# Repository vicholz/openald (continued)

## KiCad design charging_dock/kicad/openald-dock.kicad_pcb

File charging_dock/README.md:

# OpenALD Dock v1.0 — 6-slot USB-C charging dock

A charging dock for six OpenALD radios (2 rows × 3). Each radio stands USB-C-end down in a printed pocket that is
**2.00 in (50.8 mm) deep**, so the level-bar LEDs stay visible. A lead-in chamfer and a tight 0.35 mm guide zone at
the bottom centre the radio's USB-C receptacle on a vertical USB-C plug. **One USB-C PD input at the rear centre**
powers all six slots.

> **Status: design only, nothing here is hardware-validated.** ERC/DRC are clean and the CAD fit check passes, but no
> board has been built, no charger has been tested, and the plug height and insertion have not been measured on a
> real part. Treat the first build as a prototype.

Both radio variants fit the same pockets (`radio_single_board`, and `radio_adafruit_feather_rp2040` if it keeps the
lower envelope). The exact interface is in **[DOCK_INTERFACE.md](DOCK_INTERFACE.md)**.

**Plug depth (2026-11-12, still v1.0):** both radios now have their USB-C mouth **1.60 mm inside the bottom face** (the
Feather since commit 1452af8; the single board since its J1 moved 0.9 mm toward the board edge). The floor pads are
**4.00 mm** (were 3.10) and the PCB standoffs **4.1 mm** (were 5.0), so the plug goes **6.0 mm** past the mouth on both
radios (USB-C full seat 6.20 ± 0.20) while the outer size, the 50.8 mm pocket and the deck height stay the same. The
short-lived Feather riser shims (commit 0ba4451) are gone. Section view: `previews/dock_plug_insertion_per_radio.png`.
**Radios built before this change** (single board with J1 flush to the board edge, mouth 2.50) would only get 5.1 mm in this dock.

## Key numbers
| | |
|---|---|
| Outer size | **191.8 × 111.7 × 62.5 mm** (W × D × H) |
| Spacing | **25.4 mm (1.0 in)** between radios, in both X and Y |
| Pocket | 50.8 deep; 0.35 mm/side clearance for the bottom 12 mm, 0.60 above; 3 mm 45° lead-in; power-switch knob relief slot in the right wall |
| PCB | 186.0 × 105.9 mm, 2-layer, 1.6 mm, all SMT parts on top |
| Minimum charger | **USB-C PD, 45 W: must offer 20 V ≥ 2.25 A or 15 V ≥ 3 A** |
| Per-slot limit | ~1.45 A (1.09–1.81 A, SY6280 ±25 %), 5.10 V |
| Print bed | needs ≥ 192 × 112 mm for the top shell (fits 220 × 220 beds; not an A1 mini) |

## Power architecture
```
USB-C IN (J1, HRO TYPE-C-31-M-12, CC1/CC2 -> HUSB238)
  -> F1 4 A fuse (0466004.NRHF) -> D1 SMBJ22A TVS -> C1 10 uF 50 V
  -> Q1 AO4407A P-FET input switch (gate: R2 100k / R3 47k / C3 4.7 nF soft turn-on, driven by HUSB238 GATE; opens on OVP)
  -> VIN_SW, C4 100 uF 35 V
     -> U2 SY8205FCC buck A (4.7 uH MWSA0604S, 3x22 uF + 470 uF, 75k/10k -> 5.10 V) -> slots 1, 2, 4
     -> U3 SY8205FCC buck B (same)                                                   -> slots 3, 5, 6
        each slot: SY6280AAC current-limited switch (Rset 4.7k -> ~1.45 A) + 10 uF -> vertical plug VBUS,
        22k Rp on CC ("default USB power" to the radio's 5.1k Rd), plug GND + shell to GND
Status LED (light pipe in the deck between the centre pockets): green = 5 V up; red = input present but no usable PD
```
* **HUSB238** (VSET open = request up to 20 V, ISET 13.7k = 2.25 A) picks the highest PDO ≤ 20 V that offers ≥ 2.25 A,
  otherwise it steps down. D+/D− are left open (PD only).
* **Buck enable threshold:** EN divider 100k/12k from VIN_SW. The bucks turn on at 11.2–13.1 V (typ. 12.1 V). **5 V and
  9 V never enable them** (non-PD or 5 V-only chargers are safe: the dock stays off with the red LED lit). 15 V and
  20 V always enable them. **12 V-only chargers are not supported** (they may or may not start).
* Worst-case load is 6 × ~0.95 A × 5.1 V ≈ 29 W. At 20 V/2.25 A (45 W) there is about 35 % headroom after converter
  losses. Each buck is rated 5 A and carries ≤ 3 radios.

| Part | LCSC | Stock (2026-11-11 PST) | Unit |
|---|---|---|---|
| HUSB238_002DD PD sink | C7471904 | 17,771 | $0.47 |
| SY8205FCC buck ×2 | C111875 | 10,557 | $0.34 |
| SY6280AAC slot switch ×6 | C55136 | 97,877 | $0.09 |
| AO4407A input P-FET | C16072 | 19,166 | $0.33 |
| MWSA0604S-4R7MT 4.7 µH 7 A ×2 | C408457 | 8,136 | $0.17 |
| 0466004.NRHF 4 A fuse | C187596 | 14,764 | $0.08 |
| SMBJ22A TVS | C151920 | 7,664 | $0.07 |
| 100 µF 35 V / 470 µF 10 V electrolytic | C2895269 / C2858856 | 5,149 / 138,705 | $0.12 / $0.05 |
| HRO TYPE-C-31-M-12 input receptacle | C165948 | 281,637 | $0.19 |
| HX TYPE C-M 16P V-SMT vertical plug ×6 (hand solder) | C55200592 | **782** | $0.54 |

The full list is in `fab/openald-dock-BOM-human.csv` (live stock and price); `fab/cost_estimate.txt` has the cost estimate.

## Files
| Path | What |
|---|---|
| `kicad/openald-dock.kicad_{pro,sch,pcb}` | KiCad 9 project (schematic and board are generated by the scripts) |
| `fab/openald-dock-gerbers-jlcpcb.zip` | Gerbers + drill (JLCPCB) |
| `fab/openald-dock-BOM-jlcpcb.csv`, `fab/openald-dock-CPL-jlcpcb.csv` | JLC assembly BOM + CPL (JLC_CORR rotation/offset corrections applied) |
| `fab/openald-dock-centroid.csv`, `fab/openald-dock.pos` | Centroid / KiCad position files |
| `fab/openald-dock-BOM-human.csv`, `fab/cost_estimate.txt`, `fab/lcsc_lookup.json` | Human BOM with live stock and prices, cost estimate |
| `fab/erc_report.txt`, `fab/drc_report.txt`, `fab/jlc_cpl_fit.json` | Check reports |
| `case/openald_dock.scad`, `case/dock_params.scad` | OpenSCAD case (parameters generated from the PCB layout) |
| `case/dock_top_shell.stl`, `case/dock_base.stl`, `case/dock_floor_pads_x6.stl`, `case/floor_pads/*.stl` | Print-ready STLs (already in print orientation) |
| `case/dock_fit_report.txt` | Fit-check result |
| `docs/openald-dock-schematic.pdf`, `previews/*.png` | Schematic PDF, PCB/case renders, CPL overlay plots |
| `scripts/` | Generators: `run_all_pcb.sh` (symbols → schematic → ERC → board → route → post-route → DRC), `make_fab.py`, `jlc_cpl_fit.py`, `build_case.sh`, `check_dock_fit.py`, `render_pcb_previews.py`; `geom.py` is the single source of the geometry |

## Checks (2026-11-11)
* **ERC:** 0 errors, 0 warnings.
* **DRC:** 0 errors, **0 unconnected**. 75 silkscreen-only warnings (reference text overlapping copper, other silk or the board edge; cosmetic).
* **JLC placement:** `jlc_cpl_fit.py --check` → *correction table: OK*. All 80 CPL rows match the EasyEDA footprints' pads; worst pad-centre offset is 0.29 mm (SY8205 land-length difference). Overlays are in `previews/cpl_overlay_*.png`.
* **Case fit:** `case/dock_fit_report.txt` → **INTERFERENCES: 0**. This covers radio envelopes vs. shell/pads/base, plugs vs. case and radios (the plug sits inside the USB-C cavity), the PCB with its holes vs. every case part, every PCB part vs. every case part, and the case parts against each other. The closest part to the shell is the D3 LED, 0.19 mm under the light pipe. Insertion is 6.0 mm. The report lists the insertion per radio (6.00 / 6.00) and the Z stack.

## Printing (no supports)
* **Top shell:** print it deck-down, as exported. Walls, bosses, the light pipe and the pocket tubes grow straight up. The lead-in chamfers are 45°. Vent slots and the rear USB-C opening bridge ≤ 13 mm.
* **Base:** print it flat, as exported.
* **Floor pads (6):** print them top-face down, as exported (pegs up). Slot 5 (back centre) has its own STL with a relief over the rear USB-C receptacle's pads. The pads are interchangeable otherwise, but `floor_pads/` has one file per slot.
* PETG or PLA, 0.2 mm layers, 3 walls. Check the pocket guide on one radio before printing all six pads. If the fit is tight, the guide clearance is `CLR_GUIDE` in `scripts/geom.py`.

## Assembly
1. **Order the PCB** with JLC SMT assembly (gerber zip + BOM + CPL). The six vertical plugs J2–J7 are **not** in the JLC BOM, because LCSC has no EasyEDA footprint for C55200592 and JLC cannot verify its placement. Buy 6 (+1 spare) from LCSC and hand-solder them. They are 16 fine-pitch (0.8 mm) SMD pads plus 2 plated shell slots: use flux, a fine tip or hot air, and keep each plug **vertical** (a printed floor pad slipped over it works as a jig).
2. **Test before docking a radio:** plug in a ≥ 45 W PD charger. Green should light and red should stay off. Each slot should read 5.0–5.2 V on VBUS. A 5 V-only charger should give red only, with no slot voltage.
3. Press 6 M3 heat-set inserts into the shell bosses. Lay the PCB on the base standoffs and drop the six floor pads in (the pegs go into the PCB holes). Lower the shell over everything and fit 6 × **M3 × 10** screws from below (the standoffs are 4.1 mm since 2026-11-12; M3 × 12 would bottom out in the 6.5 mm insert holes).
4. Dock a radio front face (level-bar side) toward you, wheel to the right.

## Open risks and judgment calls
* **Plug height and insertion are not measured.** The HX drawing gives 11.60 (used here, 6.0 mm insertion) but also a 12.50 overall (possibly including the shell tabs that go through the board; not confirmed). Measure a soldered plug from the PCB top. If it is taller, the radios would stand on the plug: make `PAD_T` thicker and `STANDOFF` thinner by the difference in `scripts/geom.py` and rebuild (shorter screws again).
* **Receptacle depth:** the real seat depth of the HRO and CUI receptacles isn't on their drawings; 6.20 ± 0.20 is the USB-C spec value. Both radios must keep the 1.60 mm mouth; an older single board (mouth 2.50) only gets 5.1 mm.
* **Hand-soldered plugs:** fine pitch, and the plug must be perpendicular. The 0.35 mm guide clearance plus the case opening tolerate only ~0.5 mm of plug misalignment.
* **Plug supply:** only 782 in stock at LCSC, and it is the only in-stock vertical (board-mount, plug-up) USB-C plug found with a usable drawing. Buy spares early.
* **12 V fallback:** 12 V-only chargers are deliberately not supported. A 30 W charger that offers 12 V/2.5 A may or may not start the dock and could overload with six radios charging.
* **Autorouted power layout:** routing is Freerouting plus scripted widening of the high-current tracks (up to 2 mm) and GND pours on both layers. Review the buck hot loops (C11/C12 → U2/U3 → GND) in `previews/pcb_copper_*.png` before ordering.
* **Heat:** six radios charging inside 2 in pockets. Each pocket wall has vent slots into the open channels, and the deck and base are vented, but there is no fan. Watch radio temperature on the first full charge.
* **Viewing angle:** the single-board radio's level bar is centred on its front face, its three windows 27.0 / 29.8 / 32.6 mm above the rim (2026-11-11 update; see `DOCK_INTERFACE.md` §1). The back-row bars are best read from above or from the front at a downward angle.
* **While docked:** the radio's own TP4056 charge LEDs (D3/D4, near the USB end) are hidden. Charging is shown on the level bar by firmware (it reads CHRG_SENSE). The power switch is not reachable while docked; the relief slot in the right wall only clears the knob so it isn't flipped by insertion.
* **Layout margins:** the back margin is 13.5 mm (instead of 6) to fit the rear USB-C receptacle behind the back-centre pocket. The 25.4 mm spacing leaves channels wide enough for the electronics.
* **Not validated:** HUSB238 negotiation, buck stability with the chosen compensation (internal), SY6280 limits, thermals and plug mating are all untested.

## History
* v1.0 (2026-11-11): first design. The project was renamed from OpenALS to OpenALD before release, so the dock was born as "OpenALD Dock v1.0".

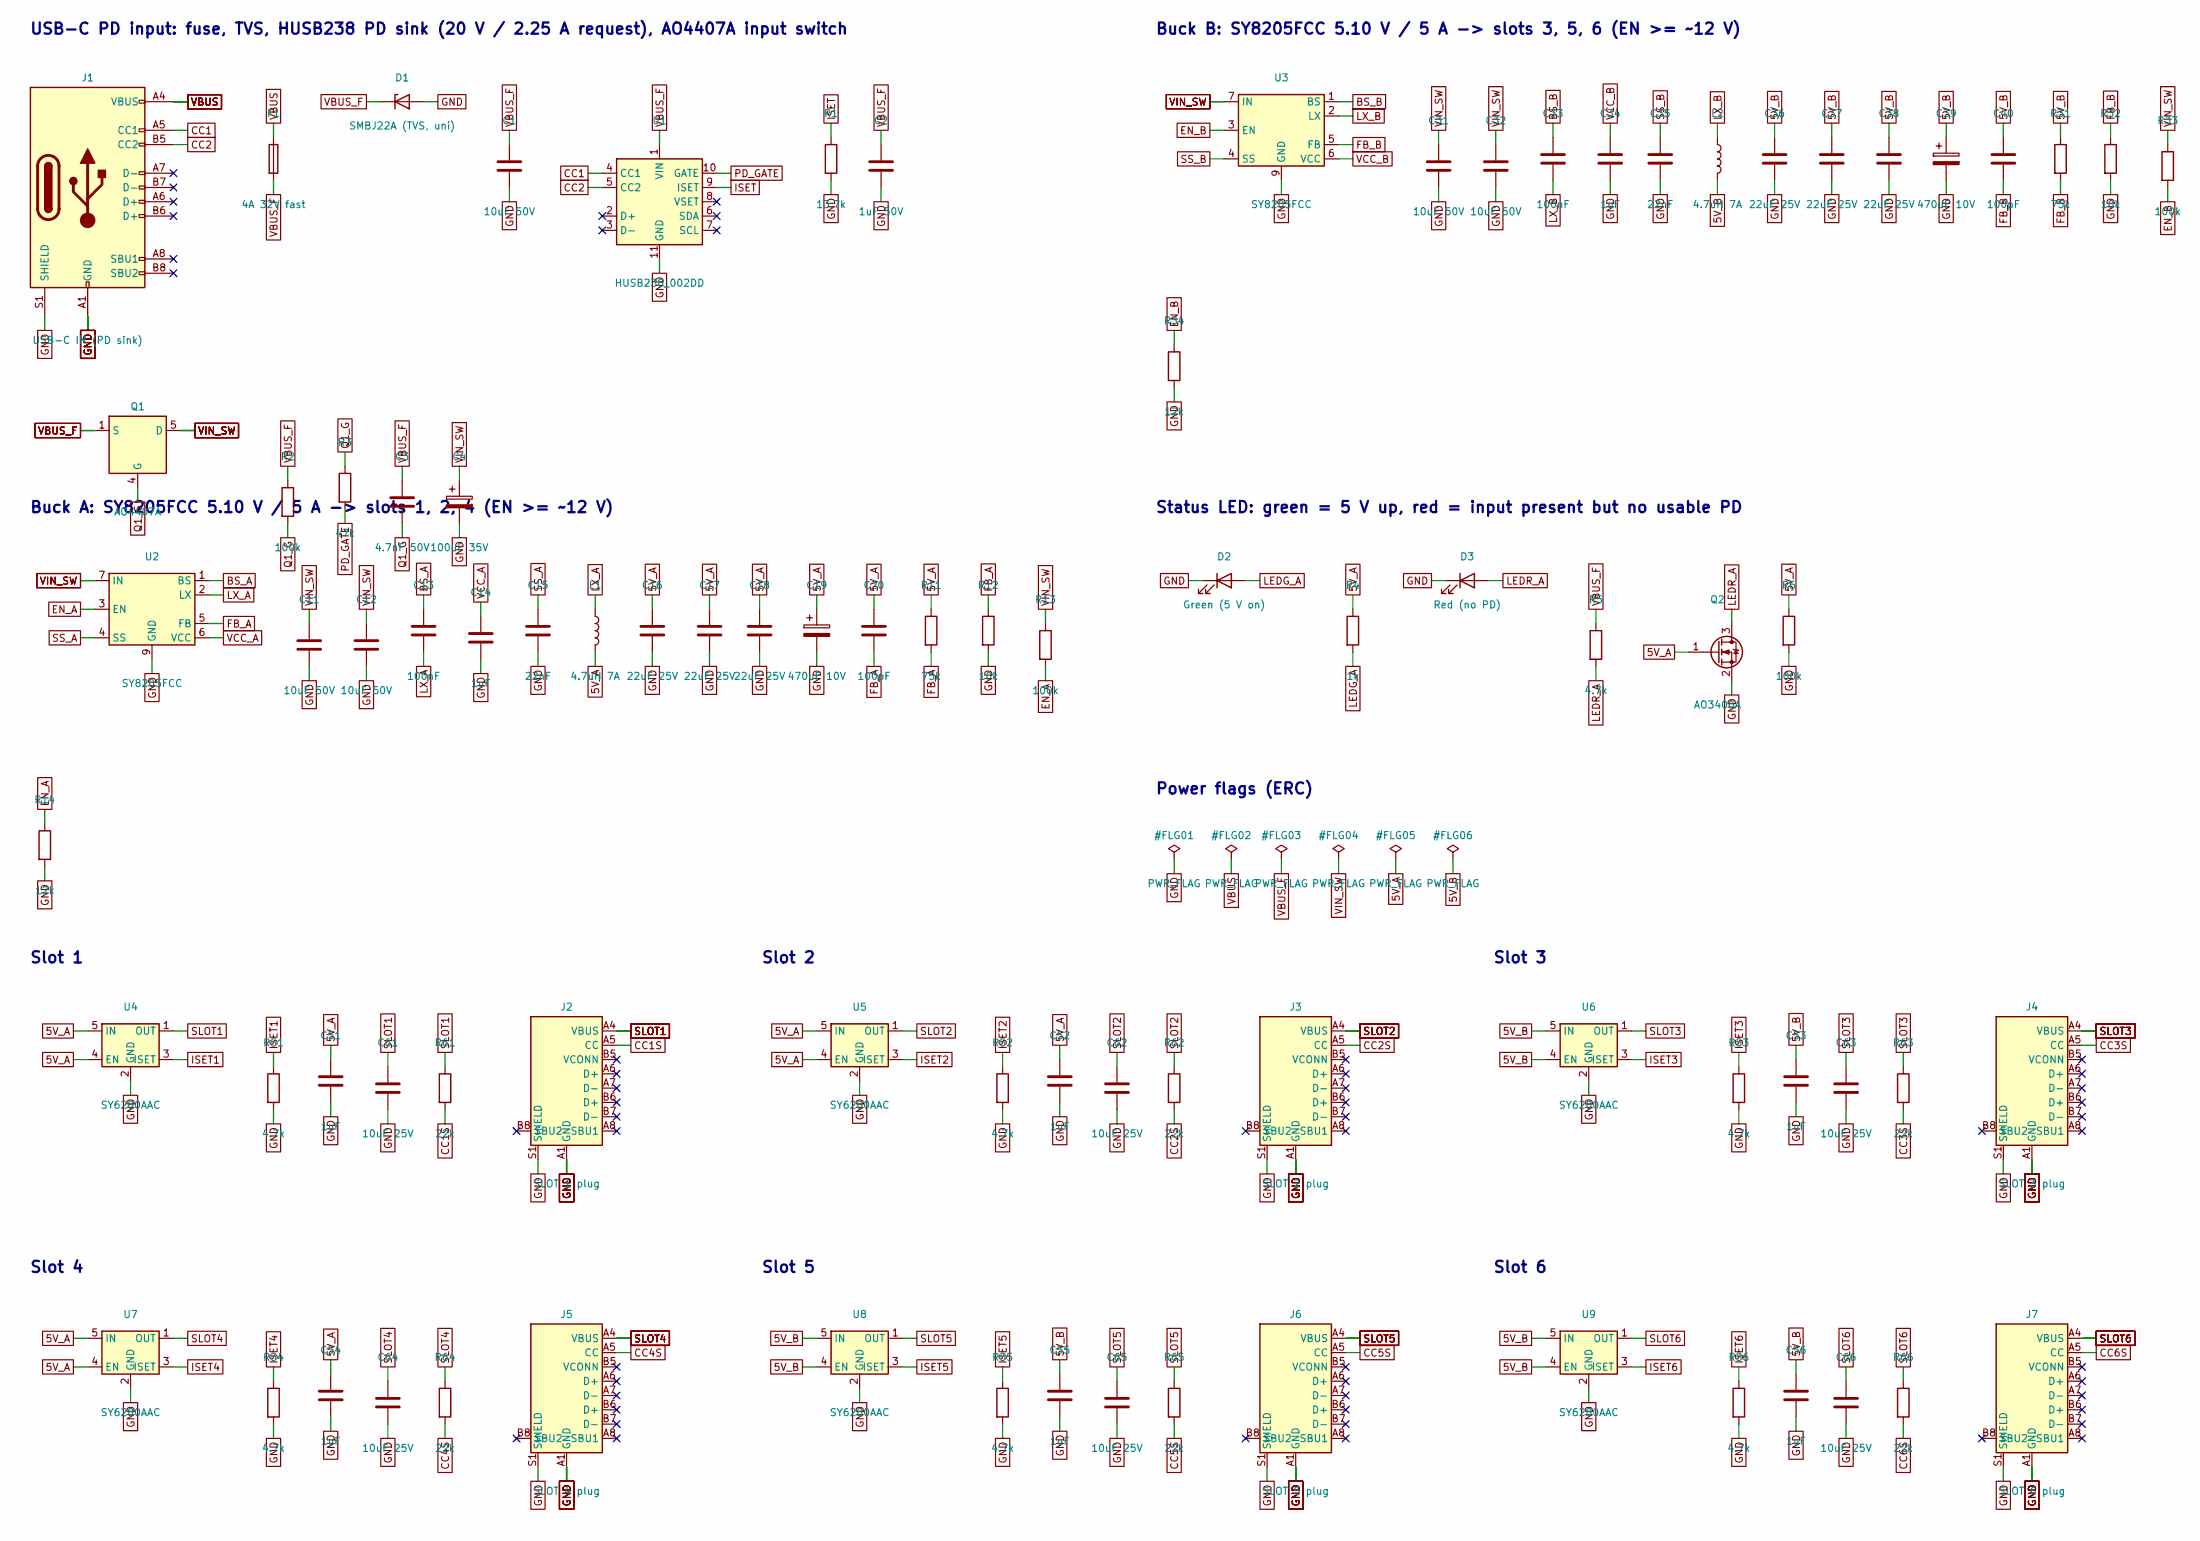
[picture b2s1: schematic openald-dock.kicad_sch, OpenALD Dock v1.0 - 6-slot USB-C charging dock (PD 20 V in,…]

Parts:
C1, C11, C12, C31, C32: 10uF 50V; C_1206_3216Metric; MPN CL31A106KBHNNNE; LCSC C13585
C2: 1uF 50V; C_0603_1608Metric; MPN CL10A105KB8NNNC; LCSC C15849
C3: 4.7nF 50V; C_0603_1608Metric; MPN 0603B472K500NT; LCSC C53987
C4: 100uF 35V; CP_Elec_8x10; MPN RVE100UF35V67RV0161; LCSC C2895269
C13, C33: 100nF; C_0603_1608Metric; MPN CC0603KRX7R9BB104; LCSC C14663
C14, C34, C51, C52, C53, C54, C55, C56: 1uF; C_0603_1608Metric; MPN CL10A105KB8NNNC; LCSC C15849
C15, C35: 22nF; C_0603_1608Metric; MPN CL10B223KB8NNNC; LCSC C21122
C16, C17, C18, C36, C37, C38: 22uF 25V; C_0805_2012Metric; MPN CL21A226MAQNNNE; LCSC C45783
C19, C39: 470uF 10V; CP_Elec_6.3x7.7; MPN RVT470UF10V67RV0159; LCSC C2858856
C20, C40: 100pF; C_0603_1608Metric; MPN CL10C101JB8NNNC; LCSC C14858
C61, C62, C63, C64, C65, C66: 10uF 25V; C_0805_2012Metric; MPN CL21A106KAYNNNE; LCSC C15850
D1: SMBJ22A (TVS, uni); D_SMB; MPN SMBJ22A; LCSC C151920
D2: Green (5 V on); LED_0603_1608Metric; MPN KT-0603G; LCSC C12624
D3: Red (no PD); LED_0603_1608Metric; MPN KT-0603R; LCSC C2286
F1: 4A 32V fast; Fuse_1206_3216Metric; MPN Littelfuse 0466004.NRHF; LCSC C187596
J1: USB-C IN (PD sink); USB_C_Receptacle_HRO_TYPE-C-31-M-12; MPN HRO TYPE-C-31-M-12; LCSC C165948
J2: SLOT 1 plug; USB_C_Plug_HX_TYPE-C-M-16P_Vertical; MPN HX TYPE C-M 16P V-SMT; LCSC C55200592
J3: SLOT 2 plug; USB_C_Plug_HX_TYPE-C-M-16P_Vertical; MPN HX TYPE C-M 16P V-SMT; LCSC C55200592
J4: SLOT 3 plug; USB_C_Plug_HX_TYPE-C-M-16P_Vertical; MPN HX TYPE C-M 16P V-SMT; LCSC C55200592
J5: SLOT 4 plug; USB_C_Plug_HX_TYPE-C-M-16P_Vertical; MPN HX TYPE C-M 16P V-SMT; LCSC C55200592
J6: SLOT 5 plug; USB_C_Plug_HX_TYPE-C-M-16P_Vertical; MPN HX TYPE C-M 16P V-SMT; LCSC C55200592
J7: SLOT 6 plug; USB_C_Plug_HX_TYPE-C-M-16P_Vertical; MPN HX TYPE C-M 16P V-SMT; LCSC C55200592
L1, L2: 4.7uH 7A; L_Sunlord_MWSA0604S; MPN Sunlord MWSA0604S-4R7MT; LCSC C408457
Q1: AO4407A; SOIC-8_3.9x4.9mm_P1.27mm; MPN AOS AO4407A; LCSC C16072
Q2: AO3400A; SOT-23; MPN AOS AO3400A; LCSC C20917
R1: 13.7k; R_0603_1608Metric; MPN 0603WAF1372T5E; LCSC C22793
R2, R6, R13, R33: 100k; R_0603_1608Metric; MPN 0603WAF1003T5E; LCSC C25803
R3: 47k; R_0603_1608Metric; MPN 0603WAF4702T5E; LCSC C25819
R4: 1k; R_0603_1608Metric; MPN 0603WAF1001T5E; LCSC C21190
R5: 4.7k; R_0805_2012Metric; MPN 0805W8F4701T5E; LCSC C17673
R11, R31: 75k; R_0603_1608Metric; MPN 0603WAF7502T5E; LCSC C23242
R12, R32: 10k; R_0603_1608Metric; MPN 0603WAF1002T5E; LCSC C25804
R14, R34: 12k; R_0603_1608Metric; MPN 0603WAF1202T5E; LCSC C22790
R51, R52, R53, R54, R55, R56: 4.7k; R_0603_1608Metric; MPN 0603WAF4701T5E; LCSC C23162
R61, R62, R63, R64, R65, R66: 22k; R_0603_1608Metric; MPN 0603WAF2202T5E; LCSC C31850
U1: HUSB238_002DD; DFN-10-1EP_3x3mm_P0.5mm_EP1.55x2.48mm; MPN Hynetek HUSB238_002DD; LCSC C7471904
U2, U3: SY8205FCC; SOIC-8-1EP_3.9x4.9mm_P1.27mm_EP2.29x3mm; MPN Silergy SY8205FCC; LCSC C111875
U4, U5, U6, U7, U8, U9: SY6280AAC; SOT-23-5; MPN Silergy SY6280AAC; LCSC C55136

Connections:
5V_A: C16.1, C17.1, C18.1, C19.1, C20.1, C51.1, C52.1, C54.1, L1.2, Q2.1 (G), R4.1, R6.1, R11.1, U4.4 (EN), U4.5 (IN), U5.4 (EN), U5.5 (IN), U7.4 (EN), U7.5 (IN)
5V_B: C36.1, C37.1, C38.1, C39.1, C40.1, C53.1, C55.1, C56.1, L2.2, R31.1, U6.4 (EN), U6.5 (IN), U8.4 (EN), U8.5 (IN), U9.4 (EN), U9.5 (IN)
BS_A: C13.1, U2.1 (BS)
BS_B: C33.1, U3.1 (BS)
CC1: J1.A5 (CC1), U1.4 (CC1)
CC1S: J2.A5 (CC), R61.2
CC2: J1.B5 (CC2), U1.5 (CC2)
CC2S: J3.A5 (CC), R62.2
CC3S: J4.A5 (CC), R63.2
CC4S: J5.A5 (CC), R64.2
CC5S: J6.A5 (CC), R65.2
CC6S: J7.A5 (CC), R66.2
EN_A: R13.2, R14.1, U2.3 (EN)
EN_B: R33.2, R34.1, U3.3 (EN)
FB_A: C20.2, R11.2, R12.1, U2.5 (FB)
FB_B: C40.2, R31.2, R32.1, U3.5 (FB)
GND: C1.2, C2.2, C4.2, C11.2, C12.2, C14.2, C15.2, C16.2, C17.2, C18.2, C19.2, C31.2, C32.2, C34.2, C35.2, C36.2, C37.2, C38.2, C39.2, C51.2, C52.2, C53.2, C54.2, C55.2, C56.2, C61.2, C62.2, C63.2, C64.2, C65.2, C66.2, D1.2 (A), D2.1 (K), D3.1 (K), J1.A1 (GND), J1.A12 (GND), J1.B1 (GND), J1.B12 (GND), J1.S1 (SHIELD), J2.A1 (GND), J2.A12 (GND), J2.B1 (GND), J2.B12 (GND), J2.S1 (SHIELD), J3.A1 (GND), J3.A12 (GND), J3.B1 (GND), J3.B12 (GND), J3.S1 (SHIELD), J4.A1 (GND), J4.A12 (GND), J4.B1 (GND), J4.B12 (GND), J4.S1 (SHIELD), J5.A1 (GND), J5.A12 (GND), J5.B1 (GND), J5.B12 (GND), J5.S1 (SHIELD), J6.A1 (GND), J6.A12 (GND), J6.B1 (GND), J6.B12 (GND), J6.S1 (SHIELD), J7.A1 (GND), J7.A12 (GND), J7.B1 (GND), J7.B12 (GND), J7.S1 (SHIELD), Q2.2 (S), R1.2, R6.2, R12.2, R14.2, R32.2, R34.2, R51.2, R52.2, R53.2, R54.2, R55.2, R56.2, U1.11 (GND), U2.9 (GND), U3.9 (GND), U4.2 (GND), U5.2 (GND), U6.2 (GND), U7.2 (GND), U8.2 (GND), U9.2 (GND)
ISET: R1.1, U1.9 (ISET)
ISET1: R51.1, U4.3 (ISET)
ISET2: R52.1, U5.3 (ISET)
ISET3: R53.1, U6.3 (ISET)
ISET4: R54.1, U7.3 (ISET)
ISET5: R55.1, U8.3 (ISET)
ISET6: R56.1, U9.3 (ISET)
LEDG_A: D2.2 (A), R4.2
LEDR_A: D3.2 (A), Q2.3 (D), R5.2
LX_A: C13.2, L1.1, U2.2 (LX)
LX_B: C33.2, L2.1, U3.2 (LX)
PD_GATE: R3.2, U1.10 (GATE)
Q1_G: C3.2, Q1.4 (G), R2.2, R3.1
SLOT1: C61.1, J2.A4 (VBUS), J2.A9 (VBUS), J2.B4 (VBUS), J2.B9 (VBUS), R61.1, U4.1 (OUT)
SLOT2: C62.1, J3.A4 (VBUS), J3.A9 (VBUS), J3.B4 (VBUS), J3.B9 (VBUS), R62.1, U5.1 (OUT)
SLOT3: C63.1, J4.A4 (VBUS), J4.A9 (VBUS), J4.B4 (VBUS), J4.B9 (VBUS), R63.1, U6.1 (OUT)
SLOT4: C64.1, J5.A4 (VBUS), J5.A9 (VBUS), J5.B4 (VBUS), J5.B9 (VBUS), R64.1, U7.1 (OUT)
SLOT5: C65.1, J6.A4 (VBUS), J6.A9 (VBUS), J6.B4 (VBUS), J6.B9 (VBUS), R65.1, U8.1 (OUT)
SLOT6: C66.1, J7.A4 (VBUS), J7.A9 (VBUS), J7.B4 (VBUS), J7.B9 (VBUS), R66.1, U9.1 (OUT)
SS_A: C15.1, U2.4 (SS)
SS_B: C35.1, U3.4 (SS)
VBUS: F1.1, J1.A4 (VBUS), J1.A9 (VBUS), J1.B4 (VBUS), J1.B9 (VBUS)
VBUS_F: C1.1, C2.1, C3.1, D1.1 (K), F1.2, Q1.1 (S), Q1.2 (S), Q1.3 (S), R2.1, R5.1, U1.1 (VIN)
VCC_A: C14.1, U2.6 (VCC)
VCC_B: C34.1, U3.6 (VCC)
VIN_SW: C4.1, C11.1, C12.1, C31.1, C32.1, Q1.5 (D), Q1.6 (D), Q1.7 (D), Q1.8 (D), R13.1, R33.1, U2.7 (IN), U2.8 (IN), U3.7 (IN), U3.8 (IN)

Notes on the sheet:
USB-C PD input: fuse, TVS, HUSB238 PD sink (20 V / 2.25 A request), AO4407A input switch
Buck A: SY8205FCC 5.10 V / 5 A -> slots 1, 2, 4 (EN >= ~12 V)
Buck B: SY8205FCC 5.10 V / 5 A -> slots 3, 5, 6 (EN >= ~12 V)
Status LED: green = 5 V up, red = input present but no usable PD
Slot 1
Slot 2
Slot 3
Slot 4
Slot 5
Slot 6
Power flags (ERC)

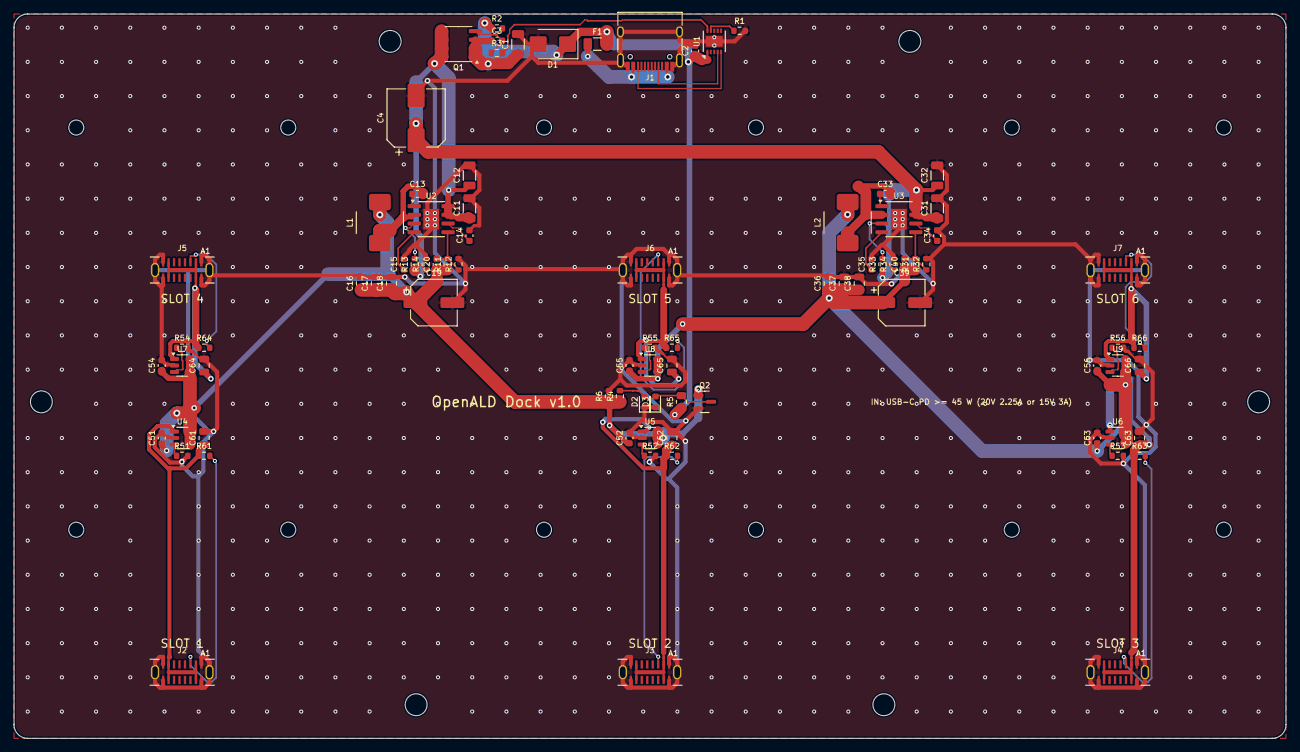
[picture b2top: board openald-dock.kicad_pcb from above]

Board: 2 copper layers, 186.0 x 105.9 mm, 104 parts (0 on the bottom side), 43 nets.

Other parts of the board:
H1, H2, H3, H4, H5, H6: M3; MountingHole_3.2mm_M3
H7, H8, H9, H10, H11, H12, H13, H14, H15, H16, H17, H18: peg; MountingHole_2.2mm_M2

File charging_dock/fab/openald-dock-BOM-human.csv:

Designator(s),Qty/board,Value / description,Manufacturer part,LCSC #,JLC library,LCSC stock (live),Unit price USD (qty 10),Assembly,Link
J1,1,USB-C IN (PD sink) (USB_C_Receptacle_HRO_TYPE-C-31-M-12),HRO TYPE-C-31-M-12,C165948,Extended,281647,0.1868,JLCPCB SMT,https://www.lcsc.com/product-detail/C165948.html
F1,1,4A 32V fast (Fuse_1206_3216Metric),Littelfuse 0466004.NRHF,C187596,Extended,14764,0.0848,JLCPCB SMT,https://www.lcsc.com/product-detail/C187596.html
D1,1,"SMBJ22A (TVS, uni) (D_SMB)",SMBJ22A,C151920,Extended,7664,0.0684,JLCPCB SMT,https://www.lcsc.com/product-detail/C151920.html
"C1,C11,C12,C31,C32",5,10uF 50V (C_1206_3216Metric),CL31A106KBHNNNE,C13585,Basic,3495621,0.127,JLCPCB SMT,https://www.lcsc.com/product-detail/C13585.html
U1,1,HUSB238_002DD (DFN-10-1EP_3x3mm_P0.5mm_EP1.55x2.48mm),Hynetek HUSB238_002DD,C7471904,Extended,17771,0.4695,JLCPCB SMT,https://www.lcsc.com/product-detail/C7471904.html
R1,1,13.7k (R_0603_1608Metric),0603WAF1372T5E,C22793,Extended,156335,0.0022,JLCPCB SMT,https://www.lcsc.com/product-detail/C22793.html
"C2,C14,C34,C51,C52,C53,C54,C55,C56",9,1uF 50V / 1uF (C_0603_1608Metric),CL10A105KB8NNNC,C15849,Basic,14039417,0.0113,JLCPCB SMT,https://www.lcsc.com/product-detail/C15849.html
Q1,1,AO4407A (SOIC-8_3.9x4.9mm_P1.27mm),AOS AO4407A,C16072,Extended,19166,0.3312,JLCPCB SMT,https://www.lcsc.com/product-detail/C16072.html
"R2,R6,R13,R33",4,100k (R_0603_1608Metric),0603WAF1003T5E,C25803,Basic,15176547,0.0029,JLCPCB SMT,https://www.lcsc.com/product-detail/C25803.html
R3,1,47k (R_0603_1608Metric),0603WAF4702T5E,C25819,Basic,2904329,0.0016,JLCPCB SMT,https://www.lcsc.com/product-detail/C25819.html
C3,1,4.7nF 50V (C_0603_1608Metric),0603B472K500NT,C53987,Basic,809197,0.0052,JLCPCB SMT,https://www.lcsc.com/product-detail/C53987.html
C4,1,100uF 35V (CP_Elec_8x10),RVE100UF35V67RV0161,C2895269,Extended,5149,0.1155,JLCPCB SMT,https://www.lcsc.com/product-detail/C2895269.html
"U2,U3",2,SY8205FCC (SOIC-8-1EP_3.9x4.9mm_P1.27mm_EP2.29x3mm),Silergy SY8205FCC,C111875,Extended,10557,0.3354,JLCPCB SMT,https://www.lcsc.com/product-detail/C111875.html
"C13,C33",2,100nF (C_0603_1608Metric),CC0603KRX7R9BB104,C14663,Basic,37431294,0.006,JLCPCB SMT,https://www.lcsc.com/product-detail/C14663.html
"C15,C35",2,22nF (C_0603_1608Metric),CL10B223KB8NNNC,C21122,Basic,993844,0.0056,JLCPCB SMT,https://www.lcsc.com/product-detail/C21122.html
"L1,L2",2,4.7uH 7A (L_Sunlord_MWSA0604S),Sunlord MWSA0604S-4R7MT,C408457,Extended,8136,0.1687,JLCPCB SMT,https://www.lcsc.com/product-detail/C408457.html
"C16,C17,C18,C36,C37,C38",6,22uF 25V (C_0805_2012Metric),CL21A226MAQNNNE,C45783,Basic,4148770,0.1055,JLCPCB SMT,https://www.lcsc.com/product-detail/C45783.html
"C19,C39",2,470uF 10V (CP_Elec_6.3x7.7),RVT470UF10V67RV0159,C2858856,Extended,138705,0.0457,JLCPCB SMT,https://www.lcsc.com/product-detail/C2858856.html
"C20,C40",2,100pF (C_0603_1608Metric),CL10C101JB8NNNC,C14858,Basic,3620383,0.0082,JLCPCB SMT,https://www.lcsc.com/product-detail/C14858.html
"R11,R31",2,75k (R_0603_1608Metric),0603WAF7502T5E,C23242,Basic,725304,0.0021,JLCPCB SMT,https://www.lcsc.com/product-detail/C23242.html
"R12,R32",2,10k (R_0603_1608Metric),0603WAF1002T5E,C25804,Basic,43350791,0.0022,JLCPCB SMT,https://www.lcsc.com/product-detail/C25804.html
"R14,R34",2,12k (R_0603_1608Metric),0603WAF1202T5E,C22790,Basic,1063579,0.0031,JLCPCB SMT,https://www.lcsc.com/product-detail/C22790.html
"U4,U5,U6,U7,U8,U9",6,SY6280AAC (SOT-23-5),Silergy SY6280AAC,C55136,Extended,97877,0.089,JLCPCB SMT,https://www.lcsc.com/product-detail/C55136.html
"R51,R52,R53,R54,R55,R56",6,4.7k (R_0603_1608Metric),0603WAF4701T5E,C23162,Basic,14761704,0.0028,JLCPCB SMT,https://www.lcsc.com/product-detail/C23162.html
"C61,C62,C63,C64,C65,C66",6,10uF 25V (C_0805_2012Metric),CL21A106KAYNNNE,C15850,Basic,8632978,0.0315,JLCPCB SMT,https://www.lcsc.com/product-detail/C15850.html
"R61,R62,R63,R64,R65,R66",6,22k (R_0603_1608Metric),0603WAF2202T5E,C31850,Basic,2498475,0.0042,JLCPCB SMT,https://www.lcsc.com/product-detail/C31850.html
D2,1,Green (5 V on) (LED_0603_1608Metric),KT-0603G,C12624,Extended,296248,0.0119,JLCPCB SMT,https://www.lcsc.com/product-detail/C12624.html
R4,1,1k (R_0603_1608Metric),0603WAF1001T5E,C21190,Basic,25734337,0.0017,JLCPCB SMT,https://www.lcsc.com/product-detail/C21190.html
D3,1,Red (no PD) (LED_0603_1608Metric),KT-0603R,C2286,Basic,6051313,0.0077,JLCPCB SMT,https://www.lcsc.com/product-detail/C2286.html
R5,1,4.7k (R_0805_2012Metric),0805W8F4701T5E,C17673,Basic,4083321,0.0034,JLCPCB SMT,https://www.lcsc.com/product-detail/C17673.html
Q2,1,AO3400A (SOT-23),AOS AO3400A,C20917,Basic,918248,0.0802,JLCPCB SMT,https://www.lcsc.com/product-detail/C20917.html
J2,1,"HX TYPE C-M 16P V-SMT vertical USB-C plug (slot 1) - hand solder, see README",HX TYPE C-M 16P V-SMT,C55200592,Extended,782,0.5431,Hand solder,https://www.lcsc.com/product-detail/C55200592.html
J3,1,"HX TYPE C-M 16P V-SMT vertical USB-C plug (slot 2) - hand solder, see README",HX TYPE C-M 16P V-SMT,C55200592,Extended,782,0.5431,Hand solder,https://www.lcsc.com/product-detail/C55200592.html
J4,1,"HX TYPE C-M 16P V-SMT vertical USB-C plug (slot 3) - hand solder, see README",HX TYPE C-M 16P V-SMT,C55200592,Extended,782,0.5431,Hand solder,https://www.lcsc.com/product-detail/C55200592.html
J5,1,"HX TYPE C-M 16P V-SMT vertical USB-C plug (slot 4) - hand solder, see README",HX TYPE C-M 16P V-SMT,C55200592,Extended,782,0.5431,Hand solder,https://www.lcsc.com/product-detail/C55200592.html
J6,1,"HX TYPE C-M 16P V-SMT vertical USB-C plug (slot 5) - hand solder, see README",HX TYPE C-M 16P V-SMT,C55200592,Extended,782,0.5431,Hand solder,https://www.lcsc.com/product-detail/C55200592.html
J7,1,"HX TYPE C-M 16P V-SMT vertical USB-C plug (slot 6) - hand solder, see README",HX TYPE C-M 16P V-SMT,C55200592,Extended,782,0.5431,Hand solder,https://www.lcsc.com/product-detail/C55200592.html
—,6,"M3 x 12 mm screws, socket or pan head (from below, heads in 3 mm counterbores)",,,,,~$0.05,Off-board,https://www.amazon.com/s?k=M3+x+12mm+socket+head+screws
—,6,"M3 brass heat-set inserts, OD 4.0-4.6 mm x L 4-5.7 mm",,,,,~$0.06,Off-board,https://www.amazon.com/s?k=M3+heat+set+inserts
—,4,10 mm round rubber bumper feet (optional),,,,,~$0.05,Off-board,https://www.amazon.com/s?k=10mm+rubber+bumper+feet
—,1,"USB-C PD charger, 45 W or more (must offer 20 V >= 2.25 A or 15 V >= 3 A) + USB-C cable",,,,,~$15-25,Off-board,https://www.amazon.com/s?k=45W+USB+C+PD+charger

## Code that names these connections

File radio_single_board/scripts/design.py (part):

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P+=[R("R1","5.1k","C23186","CC1","GND","usb","0603WAF5101T5E"), R("R2","5.1k","C23186","CC2","GND","usb","0603WAF5101T5E"),
    C("C1","10uF 25V","C15850","VBUS","GND","usb",C0805,"CL21A106KAYNNNE")]
P+=[dict(ref="U1",lib="Battery_Management:TP4056-42-ESOP8",val="TP4056",fp="Package_SO:SOIC-8-1EP_3.9x4.9mm_P1.27mm_EP2.41x3.3mm",lcsc="C16581",mpn="TP4056-42-ESOP8",grp="chg",
        pins={"1":"GND","2":"PROG","3":"GND","4":"VBUS","5":"VBAT","6":"nSTDBY","7":"nCHRG","8":"VBUS","9":"GND"})]
P+=[R("R3","1.2k","C22765","PROG","GND","chg","0603WAF1201T5E"),
    C("C2","10uF 25V","C15850","VBAT","GND","chg",C0805,"CL21A106KAYNNNE"),
    R("R21","1k","C21190","VBUS","LEDCHG_A","chg","0603WAF1001T5E"), R("R22","1k","C21190","VBUS","LEDSTB_A","chg","0603WAF1001T5E"),
    dict(ref="D3",lib="Device:LED",val="Red (charging)",fp="LED_SMD:LED_0603_1608Metric",lcsc="C2286",mpn="KT-0603R",grp="chg",pins={"1":"nCHRG","2":"LEDCHG_A"}),
    dict(ref="D4",lib="Device:LED",val="Green (charged)",fp="LED_SMD:LED_0603_1608Metric",lcsc="C12624",mpn="KT-0603G",grp="chg",pins={"1":"nSTDBY","2":"LEDSTB_A"})]
# ---------------- 18650 + DW01A/FS8205A protection ----------------
P+=[dict(ref="BT1",lib="Device:Battery_Cell",val="18650 holder",fp="Battery:BatteryHolder_MPD_BH-18650-PC",lcsc="",mpn="MPD BH-18650-PC",grp="bat",side="B",
        pins={"1":"BAT_P","2":"BATN"},hand=True)]
# ---------------- rev 4.2: reverse-polarity protection (high-side P-FET, gated by an orientation-sensing N-FET) ----------------
# Q2 (AO3401A) sits between the holder + contact (BAT_P) and every other battery node (VBAT: TP4056 BAT, DW01A VCC via R4,
# SW1, Q4, C2).  Q3 (AO3400A) senses the cell itself: its gate sees BAT_P and its source BATN (cell -), so it is on only
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# gate at its source -> Q2 off and its body diode (anode BAT_P) is reverse biased, so no loop through the board exists,
# even with USB plugged in (TP4056 driving VBAT cannot turn Q2 on, because Q3 does not look at VBAT).
P+=[dict(ref="Q2",lib="Transistor_FET:AO3401A",val="AO3401A",fp="Package_TO_SOT_SMD:SOT-23",lcsc="C15127",mpn="AOS AO3401A",grp="bat",
        pins={"1":"Q2_G","2":"VBAT","3":"BAT_P"}),
    dict(ref="Q3",lib="Transistor_FET:AO3400A",val="AO3400A",fp="Package_TO_SOT_SMD:SOT-23",lcsc="C20917",mpn="AOS AO3400A",grp="bat",
        pins={"1":"Q3_G","2":"BATN","3":"Q2_G"}),
    R("R23","10k","C25804","BAT_P","Q3_G","bat","0603WAF1002T5E"),     # Q3 gate resistor (no DC current)
    R("R24","1M","C22935","VBAT","Q2_G","bat","0603WAF1004T5E")]      # Q2 gate pull-up to its source (~4 uA while Q3 is on)
P+=[dict(ref="U2",lib="Battery_Management:DW01A",val="DW01A",fp="Package_TO_SOT_SMD:SOT-23-6",lcsc="C351410",mpn="DW01A (PUOLOP)",grp="bat",
        pins={"1":"OD","2":"CS","3":"OC","4":None,"5":"DW_VCC","6":"BATN"}),
    dict(ref="Q1",lib="openald:FS8205A",val="FS8205A",fp="Package_TO_SOT_SMD:SOT-23-6",lcsc="C2830320",mpn="FS8205A (TECH PUBLIC)",grp="bat",
        pins={"1":"BATN","2":"Q_D","3":"GND","4":"OC","5":"Q_D","6":"OD"}),
    R("R4","100","C22775","VBAT","DW_VCC","bat","0603WAF1000T5E"),
    C("C3","100nF","C14663","DW_VCC","BATN","bat",mpn="CC0603KRX7R9BB104"),
    R("R5","1k","C21190","CS","GND","bat","0603WAF1001T5E")]
# ---------------- power switch, wheel-press power path (Q4), LDO ----------------
P+=[dict(ref="SW1",lib="Switch:SW_SPDT",val="POWER (SK-12E12-G5)",fp="openald:SW_Slide_SPDT_Angled_HRO_SK-12E12-G5",lcsc="C136720",mpn="HRO SK-12E12-G5",grp="pwr",tht=True,
        pins={"1":None,"2":"VBAT","3":"VSYS"}),
    # v1.0 wheel-press update (2026-11-11): the separate battery-check button SW2 (EVQ-P7A01P, C79167) is gone. The
    # thumbwheel's push switch (SW3 S -> C = GND) now does its job: R25 holds WHEEL_SW_N (Q4 gate) at VBAT, pressing the
    # wheel pulls it to GND, P-FET Q4 turns on and drives VBTN from VBAT exactly like SW2 did (D2 -> VSYS, D10 -> VMCU,
    # R6/R7 -> BTN_SENSE). So "hold the wheel in with the switch off" still powers the MCU for the battery check, and
    # with the switch on the MCU reads every wheel press on BTN_SENSE (PC1). Released: no current (gate at source).
    # Pressed: 4.2 uA in R25. PD4 is no longer connected (WHEEL_SW_N sits at VBAT, up to 4.2 V, too high for a 3.3 V pin).
    dict(ref="Q4",lib="Transistor_FET:AO3401A",val="AO3401A",fp="Package_TO_SOT_SMD:SOT-23",lcsc="C15127",mpn="AOS AO3401A",grp="pwr",
        pins={"1":"WHEEL_SW_N","2":"VBAT","3":"VBTN"}),   # AO3401A SOT-23: 1 G, 2 S, 3 D (same as Q2)
    R("R25","1M","C22935","VBAT","WHEEL_SW_N","pwr","0603WAF1004T5E"),
    dict(ref="D2",lib="Device:D_Schottky",val="B5819W",fp="Diode_SMD:D_SOD-123",lcsc="C8598",mpn="B5819W SL",grp="pwr",pins={"1":"VSYS","2":"VBTN"}),
    # rev 4.1: 4.7k/10k (was 47k/100k). VBTN floats when SW2 (now Q4) is open, and D2/D10 (B5819W) reverse leakage (JSCJ datasheet:
    # ~5 uA each at 25 C, ~10x at 75 C) into 147k gave ~1 V on PC1 at room temperature (above VIL max) -> false "pressed".
    R("R6","4.7k","C23162","VBTN","BTN_SENSE","pwr","0603WAF4701T5E"), R("R7","10k","C25804","BTN_SENSE","GND","pwr","0603WAF1002T5E"),
    dict(ref="U5",lib="Regulator_Linear:XC6206PxxxMR",val="XC6206P332MR",fp="Package_TO_SOT_SMD:SOT-23-3",lcsc="C5446",mpn="XC6206P332MR-G",grp="pwr",
        pins={"1":"GND","2":"+3V3R","3":"VSYS"}),
    C("C4","1uF","C15849","VSYS","GND","pwr",mpn="CL10A105KB8NNNC"), C("C5","10uF","C19702","+3V3R","GND","pwr",mpn="CL10A106KP8NNNC"),
    # rev 4.1: 47k/12k (was 100k/33k). 100k/33k put a full cell (4.24 V max) at 1.05 V, above the 1.0 V minimum of the
    # ATmega328PB internal 1.1 V reference (DS40001906 VINT 1.0-1.2 V) -> ADC could clip. Now 0.86 V; source 9.6k (<10k per DS).
    R("R8","47k","C25819","VSYS","BAT_ADC","pwr","0603WAF4702T5E"), R("R9","12k","C22790","BAT_ADC","GND","pwr","0603WAF1202T5E"),
    C("C6","100nF","C14663","BAT_ADC","GND","pwr",mpn="CC0603KRX7R9BB104")]
# ---------------- MCU: ATmega328PB-AU (TQFP-32), internal 8 MHz RC; Arduino (MiniCore) pin names in comments ----------------
# Pin 3 (PE0) is tied to GND and pin 6 (PE1) to +3V3 so an ATmega328P-AU (pin 3 = GND, pin 6 = VCC) also drops in;
# firmware must leave PE0/PE1 as inputs without pull-ups (Microchip AN42559 / AT15007).
P+=[dict(ref="U3",lib="MCU_Microchip_ATmega:ATmega328PB-A",val="ATmega328PB-AU",fp="Package_QFP:TQFP-32_7x7mm_P0.8mm",lcsc="C132230",mpn="ATMEGA328PB-AU",grp="mcu",
        pins={"4":"+3V3","18":"+3V3","6":"+3V3","5":"GND","21":"GND","3":"GND","20":"AREF",
              "32":"ENC_A","1":"ENC_B","2":None,                     # PD2/INT0 (D2), PD3/INT1 (D3), PD4 (D4) spare: wheel press is read on BTN_SENSE (PC1)
              "9":"LVL1","10":"LVL2","13":"LVL3",                    # PD5/OC0B (D5), PD6/OC0A (D6), PB1/OC1A (D9): hardware PWM
              "15":"MOSI","16":"MISO","17":"SCK",                    # PB3/PB4/PB5 (D11/D12/D13): ISP only
              "23":"BAT_ADC","24":"BTN_SENSE","25":"CHRG_SENSE",     # PC0/ADC0 (A0), PC1 (A1), PC2 (A2)
              "27":"SDA","28":"SCL","29":"nRESET",                   # PC4/SDA0 (A4), PC5/SCL0 (A5), PC6/RESET
              "30":"MCU_RX","31":"MCU_TX",                           # PD0/RXD0 (D0), PD1/TXD0 (D1)
              "7":None,"8":None,"11":None,"12":None,"14":None,"19":None,"22":None,"26":None}),
    C("C7","100nF","C14663","+3V3","GND","mcu",mpn="CC0603KRX7R9BB104"),     # VCC pin 4
    C("C13","100nF","C14663","+3V3","GND","mcu",mpn="CC0603KRX7R9BB104"),    # AVCC pin 18
    C("C14","100nF","C14663","AREF","GND","mcu",mpn="CC0603KRX7R9BB104"),    # AREF pin 20 (internal 1.1 V reference)
    # TP4056 nCHRG -> PC2 through a Schottky (cathode at nCHRG): reads low only while charging; blocks back-feed into an unpowered MCU
    dict(ref="D7",lib="Device:D_Schottky",val="B5819W",fp="Diode_SMD:D_SOD-123",lcsc="C8598",mpn="B5819W SL",grp="chg",pins={"1":"nCHRG","2":"CHRG_SENSE"}),
    R("R10","10k","C25804","+3V3","nRESET","mcu","0603WAF1002T5E"),
    # I2C pull-ups go to the radio rail: with the radio unpowered (switch off, USB in) they cannot back-feed the RDA5807M
    R("R14","4.7k","C23162","+3V3R","SDA","mcu","0603WAF4701T5E"), R("R15","4.7k","C23162","+3V3R","SCL","mcu","0603WAF4701T5E"),
    dict(ref="J3",lib="Connector_Generic:Conn_02x03_Odd_Even",val="AVR-ISP pogo pads (DNP)",fp="Connector_PinHeader_2.54mm:PinHeader_2x03_P2.54mm_Vertical",lcsc="",mpn="2x3 2.54mm header / pogo (DNP)",grp="mcu",
        pins={"1":"MISO","2":"+3V3","3":"SCK","4":"MOSI","5":"nRESET","6":"GND"},dnp=True)]
# ---------------- USB serial (CH340K, powered from VBUS only) + Arduino auto-reset + MCU-only 3.3 V rail ----------------
P+=[dict(ref="U8",lib="Power_Protection:USBLC6-2SC6",val="USBLC6-2SC6",fp="Package_TO_SOT_SMD:SOT-23-6",lcsc="C7519",mpn="ST USBLC6-2SC6",grp="ser",
        pins={"1":"USB_DP","6":"USB_DP","3":"USB_DN","4":"USB_DN","5":"VBUS","2":"GND"}),
    dict(ref="U7",lib="Interface_USB:CH340K",val="CH340K",fp="Package_SO:SSOP-10-1EP_3.9x4.9mm_P1mm_EP2.1x3.3mm",lcsc="C968586",mpn="WCH CH340K",grp="ser",
        pins={"1":"USB_DP","2":"USB_DN","3":"GND","11":"GND","7":"VBUS","10":"CH_V3","8":"MCU_RX","9":"CH_RX","4":"DTR_N","5":None,"6":None}),
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
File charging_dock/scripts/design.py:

"""OpenALD Dock v1.0 - parts, values, footprints, LCSC numbers and pin->net connections (single source of truth).
Power path: USB-C in (J1) -> F1 4 A fuse -> D1 SMBJ22A TVS -> Q1 AO4407A P-FET (gated by U1 HUSB238 PD sink, opens on
no-PD/OVP) -> VIN_SW -> 2x SY8205FCC 5 A buck (U2 -> 5V_A, U3 -> 5V_B, 5.10 V, enabled only above ~12 V) -> 6x SY6280AAC
current-limited switches (~1.45 A each) -> 6 vertical USB-C plugs (J2-J7)."""
R0603="Resistor_SMD:R_0603_1608Metric"; R0805="Resistor_SMD:R_0805_2012Metric"; C0603="Capacitor_SMD:C_0603_1608Metric"
C0805="Capacitor_SMD:C_0805_2012Metric"; C1206="Capacitor_SMD:C_1206_3216Metric"
def R(ref,val,lcsc,n1,n2,grp,mpn="",fp=R0603):
    return dict(ref=ref,lib="Device:R",val=val,fp=fp,lcsc=lcsc,mpn=mpn,pins={"1":n1,"2":n2},grp=grp)
def C(ref,val,lcsc,n1,n2,grp,fp=C0603,mpn=""):
    return dict(ref=ref,lib="Device:C",val=val,fp=fp,lcsc=lcsc,mpn=mpn,pins={"1":n1,"2":n2},grp=grp)
P=[]
# ---------------- USB-C PD input ----------------
P+=[dict(ref="J1",lib="Connector:USB_C_Receptacle_USB2.0_16P",val="USB-C IN (PD sink)",fp="Connector_USB:USB_C_Receptacle_HRO_TYPE-C-31-M-12",lcsc="C165948",mpn="HRO TYPE-C-31-M-12",grp="in",
        pins={"A4":"VBUS","A9":"VBUS","B4":"VBUS","B9":"VBUS","A1":"GND","A12":"GND","B1":"GND","B12":"GND","S1":"GND",
              "A5":"CC1","B5":"CC2","A6":None,"B6":None,"A7":None,"B7":None,"A8":None,"B8":None}),   # power-only: D+/D- not used
    dict(ref="F1",lib="Device:Fuse",val="4A 32V fast",fp="Fuse:Fuse_1206_3216Metric",lcsc="C187596",mpn="Littelfuse 0466004.NRHF",grp="in",pins={"1":"VBUS","2":"VBUS_F"}),
    dict(ref="D1",lib="Device:D_Zener",val="SMBJ22A (TVS, uni)",fp="Diode_SMD:D_SMB",lcsc="C151920",mpn="SMBJ22A",grp="in",pins={"1":"VBUS_F","2":"GND"}),
    C("C1","10uF 50V","C13585","VBUS_F","GND","in",C1206,"CL31A106KBHNNNE"),
    # HUSB238 (DS v1.0): VSET open = 20 V request, ISET 13.7k = 2.25 A; picks the highest PDO <= 20 V offering >= 2.25 A,
    # else steps down (D+/D- left open: BC1.2/Apple detection unused, PD only); GATE (open drain) pulls Q1's gate low once a contract (or default 5 V) is up, releases it on OVP.
    dict(ref="U1",lib="openald:HUSB238",val="HUSB238_002DD",fp="Package_DFN_QFN:DFN-10-1EP_3x3mm_P0.5mm_EP1.55x2.48mm",lcsc="C7471904",mpn="Hynetek HUSB238_002DD",grp="in",
        pins={"1":"VBUS_F","2":None,"3":None,"4":"CC1","5":"CC2","6":None,"7":None,"8":None,"9":"ISET","10":"PD_GATE","11":"GND"}),
    R("R1","13.7k","C22793","ISET","GND","in","0603WAF1372T5E"),
    C("C2","1uF 50V","C15849","VBUS_F","GND","in",mpn="CL10A105KB8NNNC"),
    dict(ref="Q1",lib="openald:AO4407A",val="AO4407A",fp="Package_SO:SOIC-8_3.9x4.9mm_P1.27mm",lcsc="C16072",mpn="AOS AO4407A",grp="in",
        pins={"1":"VBUS_F","2":"VBUS_F","3":"VBUS_F","4":"Q1_G","5":"VIN_SW","6":"VIN_SW","7":"VIN_SW","8":"VIN_SW"}),
    R("R2","100k","C25803","VBUS_F","Q1_G","in","0603WAF1003T5E"),     # gate pull-up to source: off by default
    R("R3","47k","C25819","Q1_G","PD_GATE","in","0603WAF4702T5E"),     # Vgs = -Vin*100/147 (13.6 V at 20 V, < 20 V max)
    C("C3","4.7nF 50V","C53987","VBUS_F","Q1_G","in",mpn="0603B472K500NT"),  # slows the turn-on (inrush into C4/C5-C8)
    dict(ref="C4",lib="Device:C_Polarized",val="100uF 35V",fp="Capacitor_SMD:CP_Elec_8x10",lcsc="C2895269",mpn="RVE100UF35V67RV0161",grp="in",pins={"1":"VIN_SW","2":"GND"})]
# ---------------- 2x SY8205FCC buck, 5.10 V (Vref 0.6 V, 75k/10k) ----------------
for s,u,base in (("A","U2",10),("B","U3",30)):
    n=lambda i: f"{i}{base+0}" if False else None
    c=lambda i: f"C{base+i}"; r=lambda i: f"R{base+i}"
    P+=[dict(ref=u,lib="openald:SY8205FCC",val="SY8205FCC",fp="Package_SO:SOIC-8-1EP_3.9x4.9mm_P1.27mm_EP2.29x3mm",lcsc="C111875",mpn="Silergy SY8205FCC",grp="buck"+s,
            pins={"1":f"BS_{s}","2":f"LX_{s}","3":f"EN_{s}","4":f"SS_{s}","5":f"FB_{s}","6":f"VCC_{s}","7":"VIN_SW","8":"VIN_SW","9":"GND"}),
        C(c(1),"10uF 50V","C13585","VIN_SW","GND","buck"+s,C1206,"CL31A106KBHNNNE"),
        C(c(2),"10uF 50V","C13585","VIN_SW","GND","buck"+s,C1206,"CL31A106KBHNNNE"),
        C(c(3),"100nF","C14663",f"BS_{s}",f"LX_{s}","buck"+s,mpn="CC0603KRX7R9BB104"),
        C(c(4),"1uF","C15849",f"VCC_{s}","GND","buck"+s,mpn="CL10A105KB8NNNC"),
        C(c(5),"22nF","C21122",f"SS_{s}","GND","buck"+s,mpn="CL10B223KB8NNNC"),
        dict(ref=f"L{1 if s=='A' else 2}",lib="Device:L",val="4.7uH 7A",fp="openald:L_Sunlord_MWSA0604S",lcsc="C408457",mpn="Sunlord MWSA0604S-4R7MT",grp="buck"+s,pins={"1":f"LX_{s}","2":f"5V_{s}"}),
        C(c(6),"22uF 25V","C45783",f"5V_{s}","GND","buck"+s,C0805,"CL21A226MAQNNNE"),
        C(c(7),"22uF 25V","C45783",f"5V_{s}","GND","buck"+s,C0805,"CL21A226MAQNNNE"),
        C(c(8),"22uF 25V","C45783",f"5V_{s}","GND","buck"+s,C0805,"CL21A226MAQNNNE"),
        dict(ref=c(9),lib="Device:C_Polarized",val="470uF 10V",fp="Capacitor_SMD:CP_Elec_6.3x7.7",lcsc="C2858856",mpn="RVT470UF10V67RV0159",grp="buck"+s,pins={"1":f"5V_{s}","2":"GND"}),
        C(c(10),"100pF","C14858",f"5V_{s}",f"FB_{s}","buck"+s,mpn="CL10C101JB8NNNC"),
        R(r(1),"75k","C23242",f"5V_{s}",f"FB_{s}","buck"+s,"0603WAF7502T5E"),
        R(r(2),"10k","C25804",f"FB_{s}","GND","buck"+s,"0603WAF1002T5E"),
        # EN divider: rising threshold 1.2-1.4 V -> 11.2-13.1 V at VIN (typ 12.1 V); off below 10.3-12.1 V.
        # 5 V and 9 V never enable the bucks; 15 V and 20 V always do; 12 V is not supported.
        R(r(3),"100k","C25803","VIN_SW",f"EN_{s}","buck"+s,"0603WAF1003T5E"),
        R(r(4),"12k","C22790",f"EN_{s}","GND","buck"+s,"0603WAF1202T5E")]
# ---------------- 6x slot switch (SY6280AAC, Ilim = 6800/Rset = 1.45 A +-25 %) + plug ----------------
for i in range(1,7):
    rail="5V_A" if i in (1,2,4) else "5V_B"
    P+=[dict(ref=f"U{3+i}",lib="openald:SY6280AAC",val="SY6280AAC",fp="Package_TO_SOT_SMD:SOT-23-5",lcsc="C55136",mpn="Silergy SY6280AAC",grp=f"slot{i}",
            pins={"1":f"SLOT{i}","2":"GND","3":f"ISET{i}","4":rail,"5":rail}),
        R(f"R{50+i}","4.7k","C23162",f"ISET{i}","GND",f"slot{i}","0603WAF4701T5E"),
        C(f"C{50+i}","1uF","C15849",rail,"GND",f"slot{i}",mpn="CL10A105KB8NNNC"),
        C(f"C{60+i}","10uF 25V","C15850",f"SLOT{i}","GND",f"slot{i}",C0805,"CL21A106KAYNNNE"),
        R(f"R{60+i}","22k","C31850",f"SLOT{i}",f"CC{i}S","slot{i}" if False else f"slot{i}","0603WAF2202T5E"),   # Rp: 'default USB power'
        dict(ref=f"J{1+i}",lib="openald:USB_C_Plug_16P",val=f"SLOT {i} plug",fp="openald:USB_C_Plug_HX_TYPE-C-M-16P_Vertical",lcsc="C55200592",mpn="HX TYPE C-M 16P V-SMT",grp=f"slot{i}",hand=True,
            pins={"A1":"GND","A12":"GND","B1":"GND","B12":"GND","S1":"GND","A4":f"SLOT{i}","A9":f"SLOT{i}","B4":f"SLOT{i}","B9":f"SLOT{i}",
                  "A5":f"CC{i}S","B5":None,"A6":None,"A7":None,"B6":None,"B7":None,"A8":None,"B8":None})]
# ---------------- status LED (light pipe in the deck between the centre pockets) ----------------
P+=[dict(ref="D2",lib="Device:LED",val="Green (5 V on)",fp="LED_SMD:LED_0603_1608Metric",lcsc="C12624",mpn="KT-0603G",grp="led",pins={"1":"GND","2":"LEDG_A"}),
    R("R4","1k","C21190","5V_A","LEDG_A","led","0603WAF1001T5E"),
    dict(ref="D3",lib="Device:LED",val="Red (no PD)",fp="LED_SMD:LED_0603_1608Metric",lcsc="C2286",mpn="KT-0603R",grp="led",pins={"1":"GND","2":"LEDR_A"}),
    R("R5","4.7k","C17673","VBUS_F","LEDR_A","led","0805W8F4701T5E",fp=R0805),
    dict(ref="Q2",lib="Transistor_FET:AO3400A",val="AO3400A",fp="Package_TO_SOT_SMD:SOT-23",lcsc="C20917",mpn="AOS AO3400A",grp="led",pins={"1":"5V_A","2":"GND","3":"LEDR_A"}),
    R("R6","100k","C25803","5V_A","GND","led","0603WAF1003T5E")]   # bleeds 5V_A so Q2 turns off (red back on) when the buck stops
# ---------------- mechanical ----------------
for i in range(1,7):
    P.append(dict(ref=f"H{i}",lib="Mechanical:MountingHole",val="M3",fp="MountingHole:MountingHole_3.2mm_M3",lcsc="",mpn="M3 screw hole",grp="mech",pins={},nobom=True,boardonly=True))
for i in range(7,19):
    P.append(dict(ref=f"H{i}",lib="Mechanical:MountingHole",val="peg",fp="MountingHole:MountingHole_2.2mm_M2",lcsc="",mpn="floor-pad locating peg hole",grp="mech",pins={},nobom=True,boardonly=True))
PARTS={p["ref"]:p for p in P}
